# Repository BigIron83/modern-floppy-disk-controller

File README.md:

# Modern Floppy Disk Controller

**Revision B engineering design · 15 November 2026**

Design for a standalone Raspberry Pi OS appliance that captures and replays digital flux-transition timing on conventional 8-inch, 5.25-inch, and 3.5-inch disk drives. The drive supplies the read pulses from its analog read channel. The controller timestamps those pulses and produces timing-accurate write pulses. The Raspberry Pi handles disk formats and stores images locally.

This is an engineering specification. The P1 PCB is routed and documented. Firmware implementation and hardware validation remain pending. Model-specific drive profiles are qualified against the actual drive and manual.

The [Revision P1 hardware package](hardware/p1/README.md) includes the editable KiCad project, Nucleo harness map, and bench validation procedure.

## 1. Architecture

| Layer | Revision B design |
|---|---|
| Appliance | Raspberry Pi 4 Model B or Raspberry Pi 5 running 64-bit Raspberry Pi OS Lite, with local terminal access and optional SSH |
| Pi software | C++17 CLI and shared codec/library code, CMake, Linux spidev |
| Board link | SPI0 over the 40-pin GPIO header, with an active-low reply-ready line and a controller-reset line |
| MCU | STM32H563 with local track memory, hardware timers and DMA. Prototype with NUCLEO-H563ZI plus Pi-header and buffered drive wiring |
| Flux timing | 25 MHz reference timer, 40 ns per tick. Hardware capture of read data and index. Independent hardware compare output and DMA for playback |
| Drive connection | One active drive, keyed 34-pin PC/Shugart connection, and a separate keyed 8-inch 50-pin adapter |
| Power | Independently sized Pi and drive supplies. Pi header supplies controller logic only. Use a common signal ground and protected drive-side buffers |

Select, capture, decode, write, and verify from the Pi. Images are ordinary files on local storage. Linux handles commands and block transfers while the STM32 times read and write edges independently.

## 2. Hardware

### 2.1 Main board

- Pi header prototype map, using BCM GPIO numbering. SPI0 MOSI GPIO10/pin 19, MISO GPIO9/pin 21, SCLK GPIO11/pin 23, CE0 GPIO8/pin 24, REPLY_READY GPIO25/pin 22, CONTROLLER_RESET GPIO24/pin 18, 5 V pin 2 and GND pin 6. Use 3.3 V logic. Verify SPI alternate functions on the selected STM32 package. Hold chip select high and make the controller MISO high impedance while deselected. Drive controller reset with an open-drain stage and default it to released.
- Regulate the Pi header 5 V rail locally to 3.3 V. Budget board current with both Pi models. Keep the drive supply isolated from the Pi supply's positive rails. Include SWD, boot recovery, reset, and test points for SPI, flux timing, index, write data, write gate and hardware permit.
- Use 5 V-tolerant Schmitt receiver inputs with specified partial-power-down behavior, such as SN74LVC14A at 3.3 V. Account for inversion in timer edge selection. Use an optional drive-side pull-up network for open-collector outputs. Size the pull-ups to the drive's sink and cable-edge requirements and power them from the drive-side 5 V domain.
- Use active-low open-drain outputs. Prototype with logic-level NMOS stages qualified for gate drive at 2.5–3.3 V, with gate series resistors and pulldowns. Qualify sink current, low-level voltage, rise time, and released-state leakage on a populated ribbon. A 150 Ω pull-up at 5 V draws about 33 mA per asserted line. Never assume that lightweight CMOS GPIO can sink a vintage termination network. Install the drive terminator per its manual and avoid double termination.
- Give WRITE GATE its own hardware logic AND before the sink driver. Inputs include physical write-enable switch, valid drive-side power, adapter/direct-port permit, a live hardware write-window signal, firmware request, and write-protect clear where the selected drive exposes a valid signal. Pull the output sink off through power-on/reset. Cancel, controller reset, invalid drive state, and watchdog expiry clear the permit. Set the hardware gate deadline before playback starts, independently of DMA or the host.
- A mechanical mode switch or equivalent hardware interlock selects the direct port or the adapter. An adapter ID plus presence and drive-power sensing allows software to reject a profile mismatch. The user connects the drive and sets jumpers with power off. Key connectors, label pin 1, and run signal grounds along the ribbon.
- Externally power the drive from a supply sized for that drive's rails and startup current. Supply drive-side 5 V sensing/reference at a protected dedicated input. Verify drive requirements for 5 V, 12 V, 24 V, and any separate motor supply. Keep cabinet mains and motor wiring within the original or separately engineered drive power assembly.

### 2.2 34-pin connections

All signal names prefixed with / are active low in the standard profiles. Direct-port output mapping is selectable in software with isolated drive outputs for the configurable lines. Use a straight ribbon as the reference setup and qualify a separate PC twisted-cable profile.

| Pin | PC profile | Shugart-style profile |
|---|---|---|
| 2 | Density select, where fitted | Model-specific or unused |
| 8 | /INDEX input | /INDEX input |
| 10, 12, 14, 16 | /MOTOR A, /SELECT B, /SELECT A, /MOTOR B, respectively at controller connector | Commonly /SELECT 0, /SELECT 1, /SELECT 2, /MOTOR, respectively. Confirm drive jumpers |
| 18, 20 | /DIRECTION, /STEP | Same |
| 22, 24 | /WRITE DATA, /WRITE GATE | Same |
| 26, 28, 30 | /TRACK ZERO, /WRITE PROTECT, /READ DATA | Same |
| 32 | /SIDE SELECT | /SIDE SELECT on double-sided drives |
| 34 | Often /DISK CHANGE | Often /READY |
| Odd pins | Signal returns per drive manual and connector key | Same |

Pin 2 drive mode, pin 34 semantics, drive-select jumpers, side select, RPM and step timing belong in each profile. On a typical PC ribbon the twist swaps conductors 10–16. Firmware uses the selected connector/cable position and never asserts both select outputs.

### 2.3 Dedicated 8-inch adapter

Provide a 50-pin keyed connector or keyed IDC-to-edge harness as required. Carry buffered select, direction, step, write data, write gate, and side select, plus separately controllable head load and reduced-write-current/TG43 and profile-specific motor control where supported. Return raw read data, index, track zero, write protect, and ready. Expose additional pins only after checking the specific drive manual.

| SA800-family reference signal | 50-pin assignment to verify against drive |
|---|---|
| Reduced write current | 2, where enabled by the drive's configuration |
| Side select / head load | 14 / 18, where supported |
| Index / ready | 20 / 22 |
| Drive select | 26, 28, 30, or 32, per jumpers |
| Direction / step | 34 / 36 |
| Write data / write gate | 38 / 40 |
| Track zero / write protect / raw read data | 42 / 44 / 46 |

Keep the adapter harness profile-specific. Use the drive's raw read-data path when the manual offers alternate separated outputs or requires a jumper. For an SA800-class drive with a continuously running spindle, apply head load and wait for ready and index under the configured timing. Treat TG43 as a profile rule with a configurable threshold and polarity. Evaluate it from the known physical cylinder after seek, establish it before write gate, and reject writes on drives requiring that signal unless the adapter exposes it. Blank, missing-index, and hard-sectored media require explicit handling.

## 3. Firmware and timing

### 3.1 Capture

1. Select drive, spin up or load head, seek, and confirm the profile's ready criteria. Home by bounded outward stepping against TRACK ZERO. Invalidate the cylinder after reset, failed seek, or unexpected drive change.
2. Capture the active edge of READ DATA and the active edge of INDEX on separate channels of one timer. Use separate DMA rings, record a shared capture epoch and duration, and preserve all index events. Sample independently of buffer boundaries. Reject timer overcapture, DMA overrun, or event-storage exhaustion with a terminal status.
3. Convert consecutive read timestamps into unsigned 16-bit tick deltas. Reserve 0 as an escape followed by a little-endian 32-bit interval. Record first-edge offset and exact capture duration, even for an empty track. Store index offsets separately with 32-bit tick units. At 25 MHz a 32-bit timer wraps in about 172 s. Bound one operation well below that and handle rollover by unsigned subtraction.
4. Support indexed capture, timed capture, and profile-aware hard-sector capture. For hard sectors, retain every physical pulse and identify revolution boundaries from a verified pattern when the drive presents the sector holes. With no compatible index, capture by time and preserve the unaligned origin. Capture one revolution at a time if the requested count exceeds local capacity. Keep continuous and separately reacquired revolutions distinct in the archive.

### 3.2 Playback

1. Upload one complete write plan with intended cylinder/head, start mode, first transition offset, pulse width, intervals, and gate start/stop offsets. Check length, CRC, tick arithmetic, timing limits, and media profile. Apply precompensation at the host before upload when synthesizing a track, with parameters stored in the profile. Preserve source capture and record any changes made for the write.
2. Require physical write enable and explicit host commit, then recheck drive selection, current cylinder/head, power, readiness, index expectations, write protect, and media change. Start from a hardware-synchronized index trigger for indexed writes. Bound the wait for index. Use explicitly defined timed playback only with an appropriate profile and a known write window.
3. Prime the compare timer with the first scheduled edge. A timer compare toggles the write-data output and requests DMA to load the next absolute compare time. Expand compact track intervals into alternating assertion and release times in two small DMA buffers, then refill halves ahead of use. Specify the actual write-data pulse width from the drive manual and program a separately bounded hardware gate window. Use a guard/sentinel and verify service margin with DMA contending for the bus. If the next data block cannot be supplied before its deadline or a timer/DMA fault occurs, force gate inactive and return an incomplete-write status. Playback requires no track data transfers after commit.
4. End at the specified splice within the measured target revolution. Match target RPM where required with explicit host rescaling or regeneration. Abort before writing if the requested window cannot fit. Verify with an independent readback and report sector CRC mismatch or flux-quality differences according to format. A media write can be partial after interruption, so identify the affected track and block automatic retries.

### 3.3 Initial engineering budgets

| Parameter | Design target |
|---|---|
| Timebase | 25 MHz from a crystal-referenced clock tree. Verify actual clock, tick conversion, and temperature behavior |
| Peak event workload | Qualify 1 million flux pulses/s and at least 2 million write compare updates/s for synthetic stress. Pulse width and minimum spacing remain profile-specific |
| DMA load | 4 MB/s for raw read timestamps at the stress rate or 8 MB/s for write compare timestamps. Budget two 1,024-entry 32-bit write DMA halves, each providing approximately 512 µs refill time at 2 million compare events/s |
| Track buffer | 480 KiB design allocation in DMA-eligible SRAM with bank, alignment, and cache/coherency mapping checked before layout signoff. Separate ring buffers, index, SPI, stack and diagnostics allocations |
| Track sizing | At 300 RPM and 1 million pulses/s a revolution is 200 ms and approximately 400 kB at two bytes per pulse. At 360 RPM it is about 333 kB. Sparse long intervals use the escape encoding. Multiple revolutions fit according to actual encoded size |
| Read transfer | Transfer captured blocks after completion. Benchmark sustained SPI throughput on both Pi models. At 4 MHz, the two-transaction framing limits useful throughput to less than 0.25 MB/s. At a measured 0.2 MB/s, a 400 kB revolution takes about 2 s, in addition to seek, acquisition, and rotation wait |

Select TIM2/TIM5 roles, channels, trigger routing and GPDMA requests using the package alternate-function tables, reference manual, and Nucleo board schematic before PCB layout. Prove simultaneous read/index capture and buffered write compare timing on the bench before freezing the design.

## 4. Internal SPI protocol

The Pi is SPI master and the STM32 is slave. Start at 4 MHz, mode 0, MSB first. Qualify higher rates on both Pi models after measuring signal integrity and DMA behavior. Reserve GPIO25 for a reply-ready level asserted only after the MCU has staged a complete response and armed SPI transfer DMA.

**Wire frame.** Little-endian fields in this order. ASCII magic `FDC1` (4 bytes), major and minor version (1 byte each), opcode (uint16), request ID (uint32), payload length (uint32), and payload CRC-32/ISO-HDLC (uint32). Payload follows. A request occupies one 1,024-byte CE0 transaction, padded with zeros. After REPLY_READY asserts, clock a separate 1,024-byte reply transaction with zero-filled MOSI. Limit payloads to 1,004 bytes, including metadata, and validate lengths before use. Replies use opcode bit 15, echo the request ID, and begin with uint16 status and uint16 reserved. Post long operations immediately and poll progress through subsequent commands so cancellation stays available. Keep one command/reply exchange outstanding. After the reply, the MCU deasserts REPLY_READY once the next request receiver is armed. The Pi waits for that level before sending another command. Use offset-addressed data blocks and a CRC over the full staged object.

Unexpected transaction sizes or invalid frames discard the staged command and invalidate write authorization. On timeout, re-establish a known protocol state by controller reset and HELLO. Commit is never automatically retried. Reset drops the gate and invalidates position and write authorization. During an already committed write, the hardware deadline remains effective if the Pi stops communicating.

| Opcode | Operation |
|---|---|
| 0x0001 / 0x0002 | HELLO / GET_STATUS. Return protocol version, board/firmware version, tick rate, limits, adapter identity, drive inputs, and active operation state |
| 0x0010–0x0013 | SET_PROFILE, SELECT_DRIVE, HOME, SEEK. Validate seek bounds, track step multiplier, and profile identity |
| 0x0020–0x0022 | CAPTURE, READ_CAPTURE_BLOCK, RELEASE_CAPTURE. CAPTURE returns an operation handle and completed data stays available until released or session reset |
| 0x0030–0x0033 | BEGIN_WRITE, WRITE_BLOCK, ARM_WRITE, COMMIT_WRITE. Stage by offset, verify full CRC and profile, then issue a short-lived one-use token scoped to the plan and media state |
| 0x0040 | CANCEL. Stop active hardware operation, invalidate write token, and report whether a write window was entered |

Operation errors include invalid profile, no adapter, no index, no ready, write protected, write disabled, invalid timing, geometry limit, overflow, CRC failure, DMA fault, and interrupted write. Poll operation progress with GET_STATUS. Do not automatically replay COMMIT_WRITE after a timeout. A reconnect requires the host to inspect state or read the affected track before a new write attempt. Support recovery firmware update independently of the main protocol, with a physical boot/recovery path.

## 5. Raspberry Pi OS software

- **Operating system.** Qualify a named 64-bit Raspberry Pi OS Lite image on both Pi 4 and Pi 5 and record its release and kernel build. Enable SPI through `raspi-config`. Default to SPI0 CE0 (`/dev/spidev0.0`), with an override for device path and SPI rate. Use libgpiod for reply-ready and controller reset, discovering the header GPIO controller by label or line identifiers. Avoid fixed gpiochip numbers across Pi models.
- **Deployment.** Build a native arm64 package with CMake. Install an unprivileged CLI and grant the operator access to the SPI device and necessary GPIO lines. Serialize hardware access with an exclusive local lock held throughout each operation. Run locally from a terminal or remotely through SSH. Handle terminal hangup by attempting cancellation when the process can still reach the board. Controller-side gate limits apply independently.
- **Commands.** Provide `list`, `drive-test`, `capture`, `decode`, `write`, and `verify`. Add head, cylinder, revolution and profile selection to the media operations. Keep decoding available offline. Require an explicit write command and the physical write-enable switch. Check free space before full-disk capture, retain completed tracks across interruptions, and finalize the archive after validation.
- **Data and profiles.** Save to a user-selected local directory, with support for mounted removable storage. Use versioned drive profiles for geometry, step timing, RPM range, electrical signal roles and write timing. Keep media format definitions separate. Use stable exit codes and machine-readable diagnostics for scripting.

### 5.1 Images and formats

- Archive the raw transition timing and index events first. Keep actual tick rate, cylinder/head, revolution boundaries or capture offsets, profile, RPM estimate, and quality flags with the record. Document the native format and include CRCs. Add SCP import/export with round-trip checks and flag metadata that cannot be preserved in an export.
- Qualify IBM-style FM and MFM sector decode and encode first, then qualify Amiga MFM and Commodore/Apple GCR separately with known-good disks. Preserve sector CRCs and status for reads. Keep standard sector images as derivatives when the format permits them.
- Use a 34-pin drive appropriate to the media when it can physically read and write the format. Original Sony Macintosh mechanisms, Apple Disk II mechanisms and proprietary drives require dedicated electrical adapters where their control interfaces differ. Macintosh 400K/800K variable-speed writes require a qualified mechanism and playback profile. Treat those, 2.88 MB ED, and hard-sector write modes as separately qualified extensions. Preserve multi-revolution variations and report when a drive cannot reproduce observed weak-bit, splice, or protection behavior.
- Match drive head width to the media when writing. In particular, qualify 48-TPI 5.25-inch media in a native 48-TPI mechanism. A 96-TPI drive can double-step for compatible reads but leaves a narrower written track.

## 6. Prototype and acceptance

| Stage | Required evidence |
|---|---|
| Electrical and timing bench | Measure TTL levels, sink current, idle state, rise/fall times, and decode at the drive connector with realistic termination. Inject synthetic read/index patterns through the receiver, sweep minimum pulse width and spacing, and compare timestamps to a calibrated generator. Check repeatable read/write edge error after accounting for fixed propagation delay. Initial acceptance target is ±2 ticks (80 ns) against the fixture, subject to characterization |
| Fail-safe bench | Observe gate at reset, boot, Pi reboot, SPI reset and a stalled Pi process, failed arming, power interruption, write-protect assertion, and forced DMA starvation. Confirm gate never asserts without a valid plan and that active gate clears on detected fault and by the independent deadline. Measure the actual fault-to-gate-off latency |
| 3.5-inch | PC interface HD mechanism. Capture and decode known-good 720 KB and 1.44 MB media, write expendable disks, then verify with an independent controller or legacy system |
| 5.25-inch | Test a native 360 KB drive and a 1.2 MB drive. Verify density, seek and RPM profiles, read at least one original disk per format, and write and independently verify scratch media |
| 8-inch | Qualify an SA800/801-class single-sided FM drive, then a compatible double-sided 8-inch drive for MFM. Verify head load, raw data, ready, index, physical-cylinder tracking, reduced write current behavior across its threshold, and read/write interoperability on scratch disks |
| Pi OS and archival | On both Pi 4 and Pi 5, test startup, SPI detection, transfer under storage and CPU load, cancellation, interrupted SPI, controller reset, and archive round trips. Test missing index, buffer exhaustion, known bad CRC, malformed requests, and Pi reset during a scratch-disk write |

First prototype milestone is a 3.5-inch write/readback on Raspberry Pi OS via SPI to a Nucleo board and 34-pin buffer board, plus timing and gate measurements from a logic analyzer. Bring up 5.25-inch and 8-inch drive profiles on the same firmware before committing to a production PCB. Maintain qualified profile entries by make, model, revision, jumper settings, cable type and supported formats.

## Sources

- [STMicroelectronics STM32H563/573 product line](https://www.st.com/en/microcontrollers-microprocessors/stm32h563-573.html) and [STM32H563 reference documentation](https://www.st.com/en/microcontrollers-microprocessors/stm32h563-573/documentation.html)
- [STMicroelectronics GPDMA application note AN5593](https://www.st.com/resource/en/application_note/an5593-how-to-use-the-gpdma-for-stm32-mcus-stmicroelectronics.pdf)
- [Texas Instruments SN74LVC14A specifications](https://www.ti.com/product/SN74LVC14A)
- [Shugart SA800/801 OEM and service manuals, Bitsavers](https://bitsavers.trailing-edge.com/pdf/shugart/SA8xx/)
- [SA800/801 50-pin interface table](https://allpinouts.org/pinouts/connectors/data_storage/8-floppy-diskdrive/)
- [Greaseweazle raw flux tools](https://github.com/keirf/greaseweazle) and [FluxEngine](https://github.com/davidgiven/fluxengine)
- [Raspberry Pi OS configuration and SPI enablement](https://www.raspberrypi.com/documentation/computers/configuration.html)
- [Raspberry Pi 4 header and GPIO assignments](https://pip-assets.raspberrypi.com/categories/545-raspberry-pi-4-model-b/documents/RP-008341-DS-1-raspberry-pi-4-datasheet.pdf)

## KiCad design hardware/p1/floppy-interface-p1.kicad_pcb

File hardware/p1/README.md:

# Modern Floppy Disk Controller – Routed Interface PCB P1

KiCad 9 routed prototype for the Revision B Raspberry Pi OS appliance. The board is 147 × 138 mm with four M3 mounting holes. It connects by ribbon to the Raspberry Pi 4/5 and by a prototype harness to an STM32H563 Nucleo. The STM32 retains the hardware flux capture, write playback and write deadline. The PCB is a signal interface board with through-hole pads throughout.

## Files

- [Bill of materials](BOM.md) lists quantities and U.S. supplier references for the board and harness.

- `floppy-interface-p1.kicad_pcb` is the editable routed PCB. Open it from `floppy-interface-p1.kicad_pro`.
- `pad-net-map.csv` records footprint pins and intentional no-connect pads.
- `routed-top.png` previews the copper and top silkscreen.
- `floppy-interface-p1.kicad_sch`, `fdc-p1.kicad_sym` and `sym-lib-table` provide the editable schematic and its project-local parts. `schematic.pdf` is the print view.
- `nucleo-j4-harness.csv` specifies the 30 harness positions. `bench-validation.md` covers power selection, bridge settings, timers, DMA and hardware acceptance.
- `erc.txt` and `drc.txt` record ERC, DRC, connectivity and schematic-to-PCB parity.

The board uses two copper layers. Nominal widths are 0.25 mm for signals, 0.60 mm for the +5 V and 3.3 V supplies, and 0.45 mm for ground. Local neck-downs reach 0.15 mm. Nominal routing clearance is 0.22 mm, with 0.60 mm vias and 0.30 mm drills. The bottom layer also has a ground fill.

## Connectors and assembly

| Ref | Connection |
|---|---|
| J1 | Keyed 40-pin cable to the Pi GPIO header. Orient conductor 1 at both ends. |
| J2 | Keyed 34-pin 3.5-inch or 5.25-inch connector. Use a straight ribbon for first bring-up and select the appropriate PC or Shugart profile. |
| J3 | Keyed 50-pin connector for a Shugart-style 8-inch drive. Fit a keyed IDC-to-drive-edge harness when needed. This mapping brings out a single drive-select line on pin 26, head load on pin 18 and TG43/reduced write current on pin 2. Qualify the intended drive's pin functions and jumpers. |
| J4 | Keyed 30-pin STM32 module breakout. This is a custom signal harness. Use the included J4 harness CSV. |
| J5 | Drive-side regulated +5 V sense/pull-up input, pin 1 positive, pin 2 ground. Drive power is supplied separately. |
| JP1 | Physical write-enable shunt. Default assembly is shunt removed. |
| TP1–TP6 | Index, read data, write data, write gate, write window, and ground. |

J1–J4 use square pin-1 pads, silkscreen numerals and connector orientation marks. J5 and JP1 have a pin-1 numeral. U1–U5 show pin 1 and the package notch. Verify the shroud key and red stripe on each actual cable.

Connect **one drive at a time**, with both systems powered off while changing cables. The two drive headers share drive signals. The 8-inch spindle/head-load arrangement is intended for the SA800-style baseline and must be checked for the actual mechanism. The 8-inch interface does not provide general-purpose motor-on or special control signals on optional pins. J5 takes the drive's regulated logic rail. It does not feed drive motor or logic power. Keep Pi and drive positive rails separate, with a common signal ground.

## Parts and circuit

| References | Preliminary parts |
|---|---|
| U1–U2 | Socketed SN74LS06N PDIP open-collector drivers. Check sink current and VOL against the selected drive termination. |
| U3–U4 | SN74LVC14A on pin-for-pin SOIC-14 to DIP-14 carriers. The carrier leads are through-hole at the baseboard. Verify carrier envelope and orientation. These two modules and the STM32 development board contain the surface-mount devices in the design. |
| U5 | Socketed CD74HCT21E PDIP gate for firmware request, timer window, physical arm and write-protect clear. Verify thresholds, propagation and power-up behavior. |
| RN1–RN2 | Bussed 1 kΩ ×6 SIP pulldowns, common at pin 1. Check the selected MCU GPIO drive budget against simultaneous assertions. |
| RN3 | Bussed 2.2 kΩ ×6 SIP drive-input pull-ups, common to DRIVE_5V at pin 1. Check original drive output type and termination. Recalculate if the actual pull-up configuration differs. |
| R1–R8, Q1, C1–C5 | Axial resistors, pinout-qualified TO-92 reset MOSFET and radial 100 nF ceramic bypass capacitors. The TO-92 footprint expects source, gate, drain on pads 1, 2, 3. |
| J1–J5, JP1, TP1–TP6 | Through-hole keyed headers, shunt and test pads. |

Receiver outputs are inverted relative to the active-low drive lines. The drive +5 V sense path produces the source for the write-enable jumper through two receive gates. The write gate is active low at the connector. Drive-side write protect is interpreted as asserted low. With no drive connected, the pull-up can indicate a clear write-protect state, so firmware must also validate drive selection and media state before arming.

## Verification and prototype status

KiCad ERC and DRC completed with zero reported violations, zero unresolved connections, and zero schematic-parity differences. All 284 numbered pads were compared with the schematic and original pin map, including intentional no-connects. PCB copper routes and connector placement were preserved.

The Nucleo harness assignments and peripheral functions were checked against ST's documentation. The board and harness still require assembly and physical validation. Follow the bench validation procedure before attaching archival media.

## References

- [Shugart SA800/801 OEM and service manuals](https://bitsavers.trailing-edge.com/pdf/shugart/SA8xx/)
- [SA800-family interface reference](https://allpinouts.org/pinouts/connectors/data_storage/8-floppy-diskdrive/)
- [STM32H563 Nucleo board](https://www.st.com/en/evaluation-tools/nucleo-h563zi.html)
- [Raspberry Pi GPIO header documentation](https://www.raspberrypi.com/documentation/computers/raspberry-pi.html)
- [TI SN74LS06](https://www.ti.com/product/SN74LS06), [TI SN74LVC14A](https://www.ti.com/product/SN74LVC14A), [TI CD74HCT21](https://www.ti.com/lit/ds/symlink/cd74hct21.pdf)

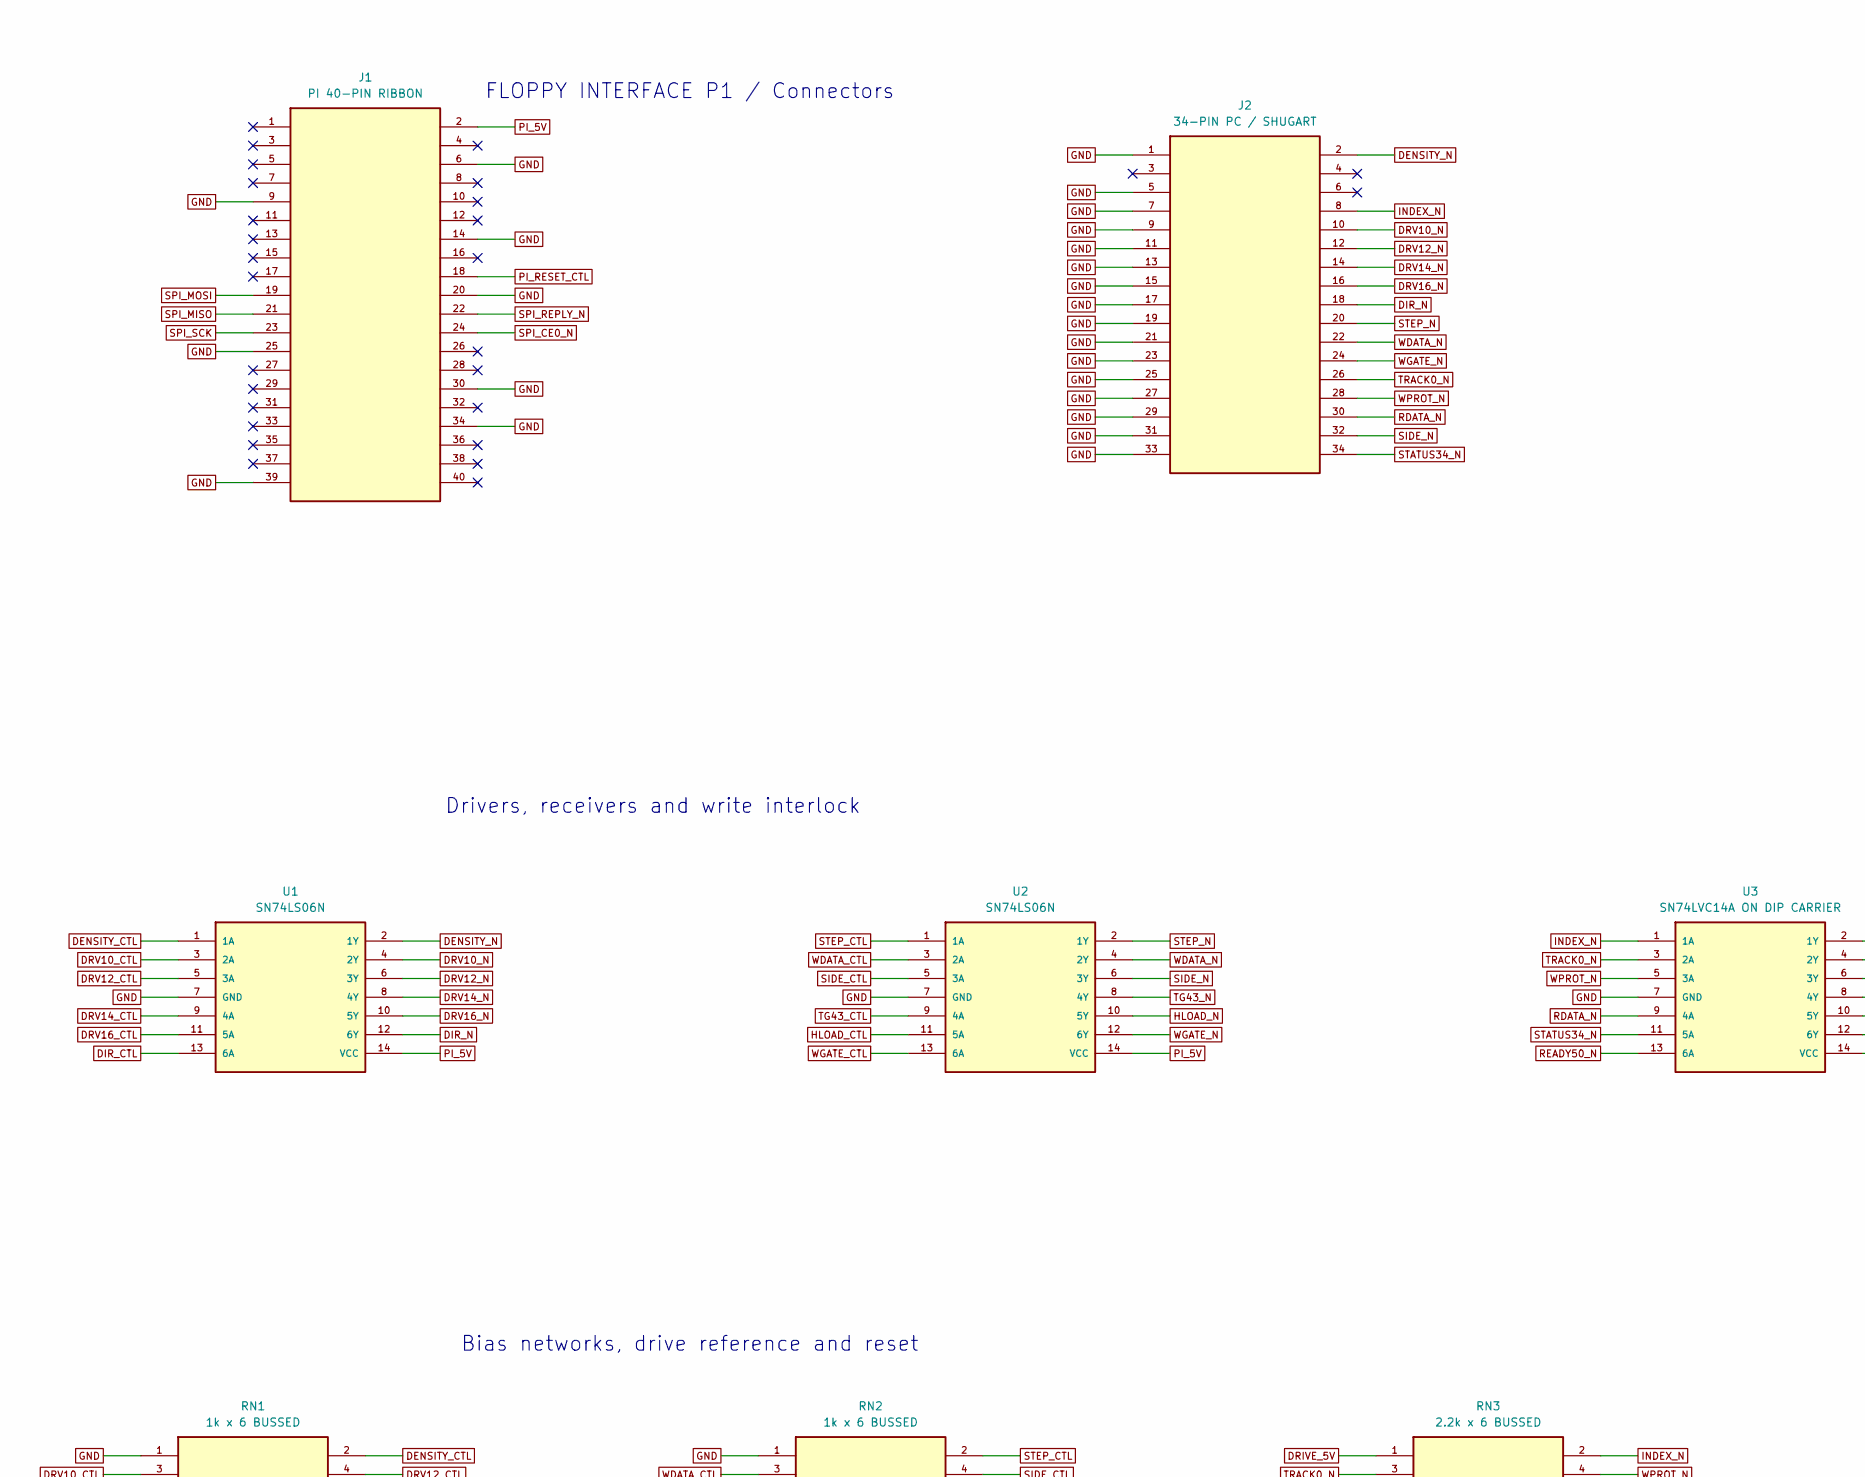
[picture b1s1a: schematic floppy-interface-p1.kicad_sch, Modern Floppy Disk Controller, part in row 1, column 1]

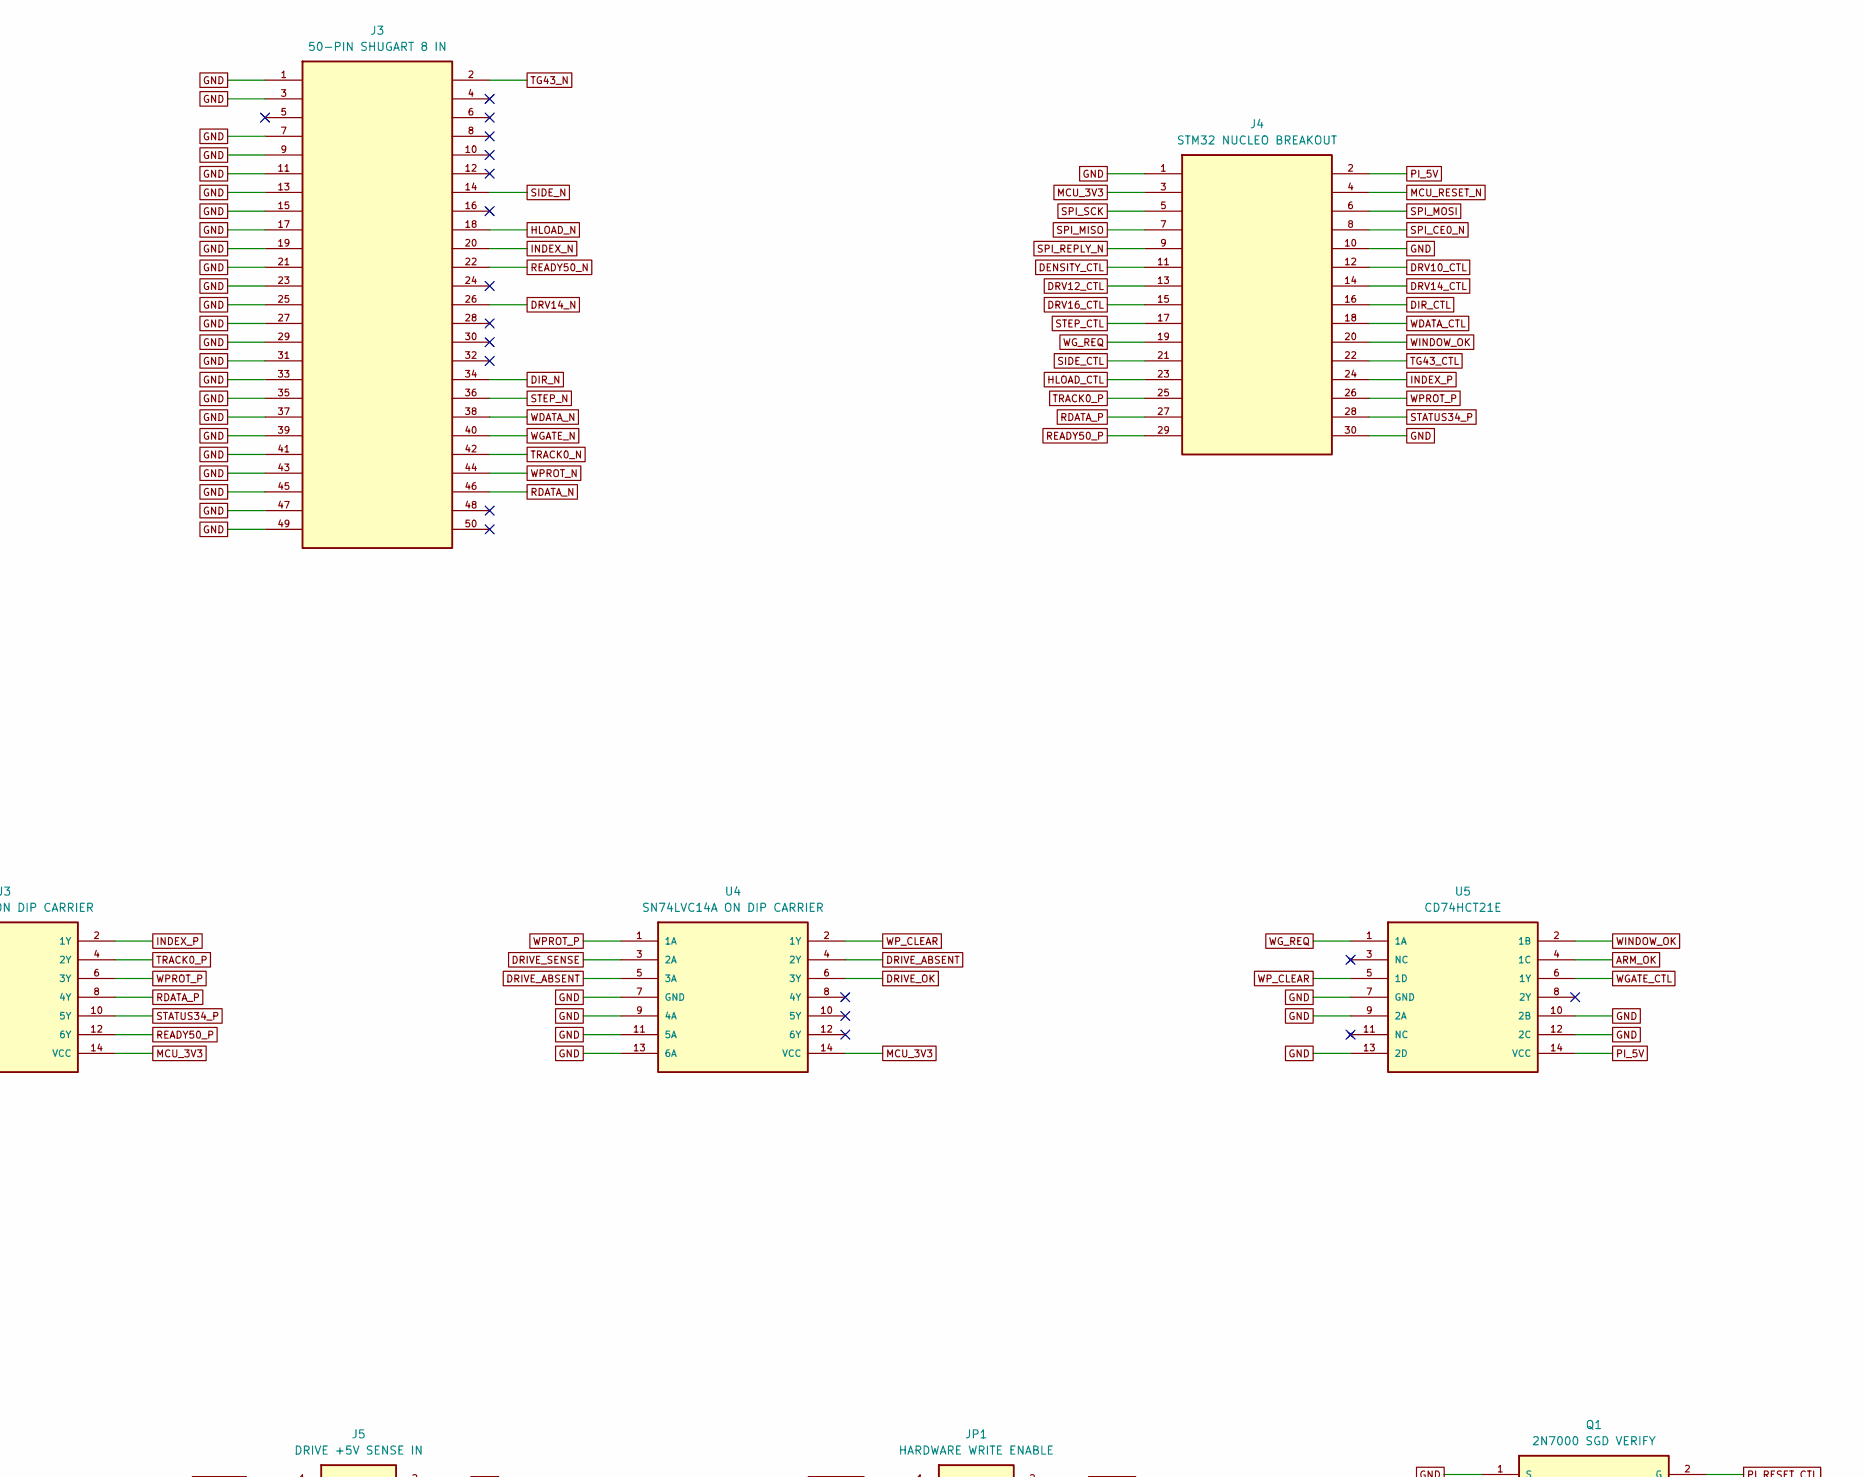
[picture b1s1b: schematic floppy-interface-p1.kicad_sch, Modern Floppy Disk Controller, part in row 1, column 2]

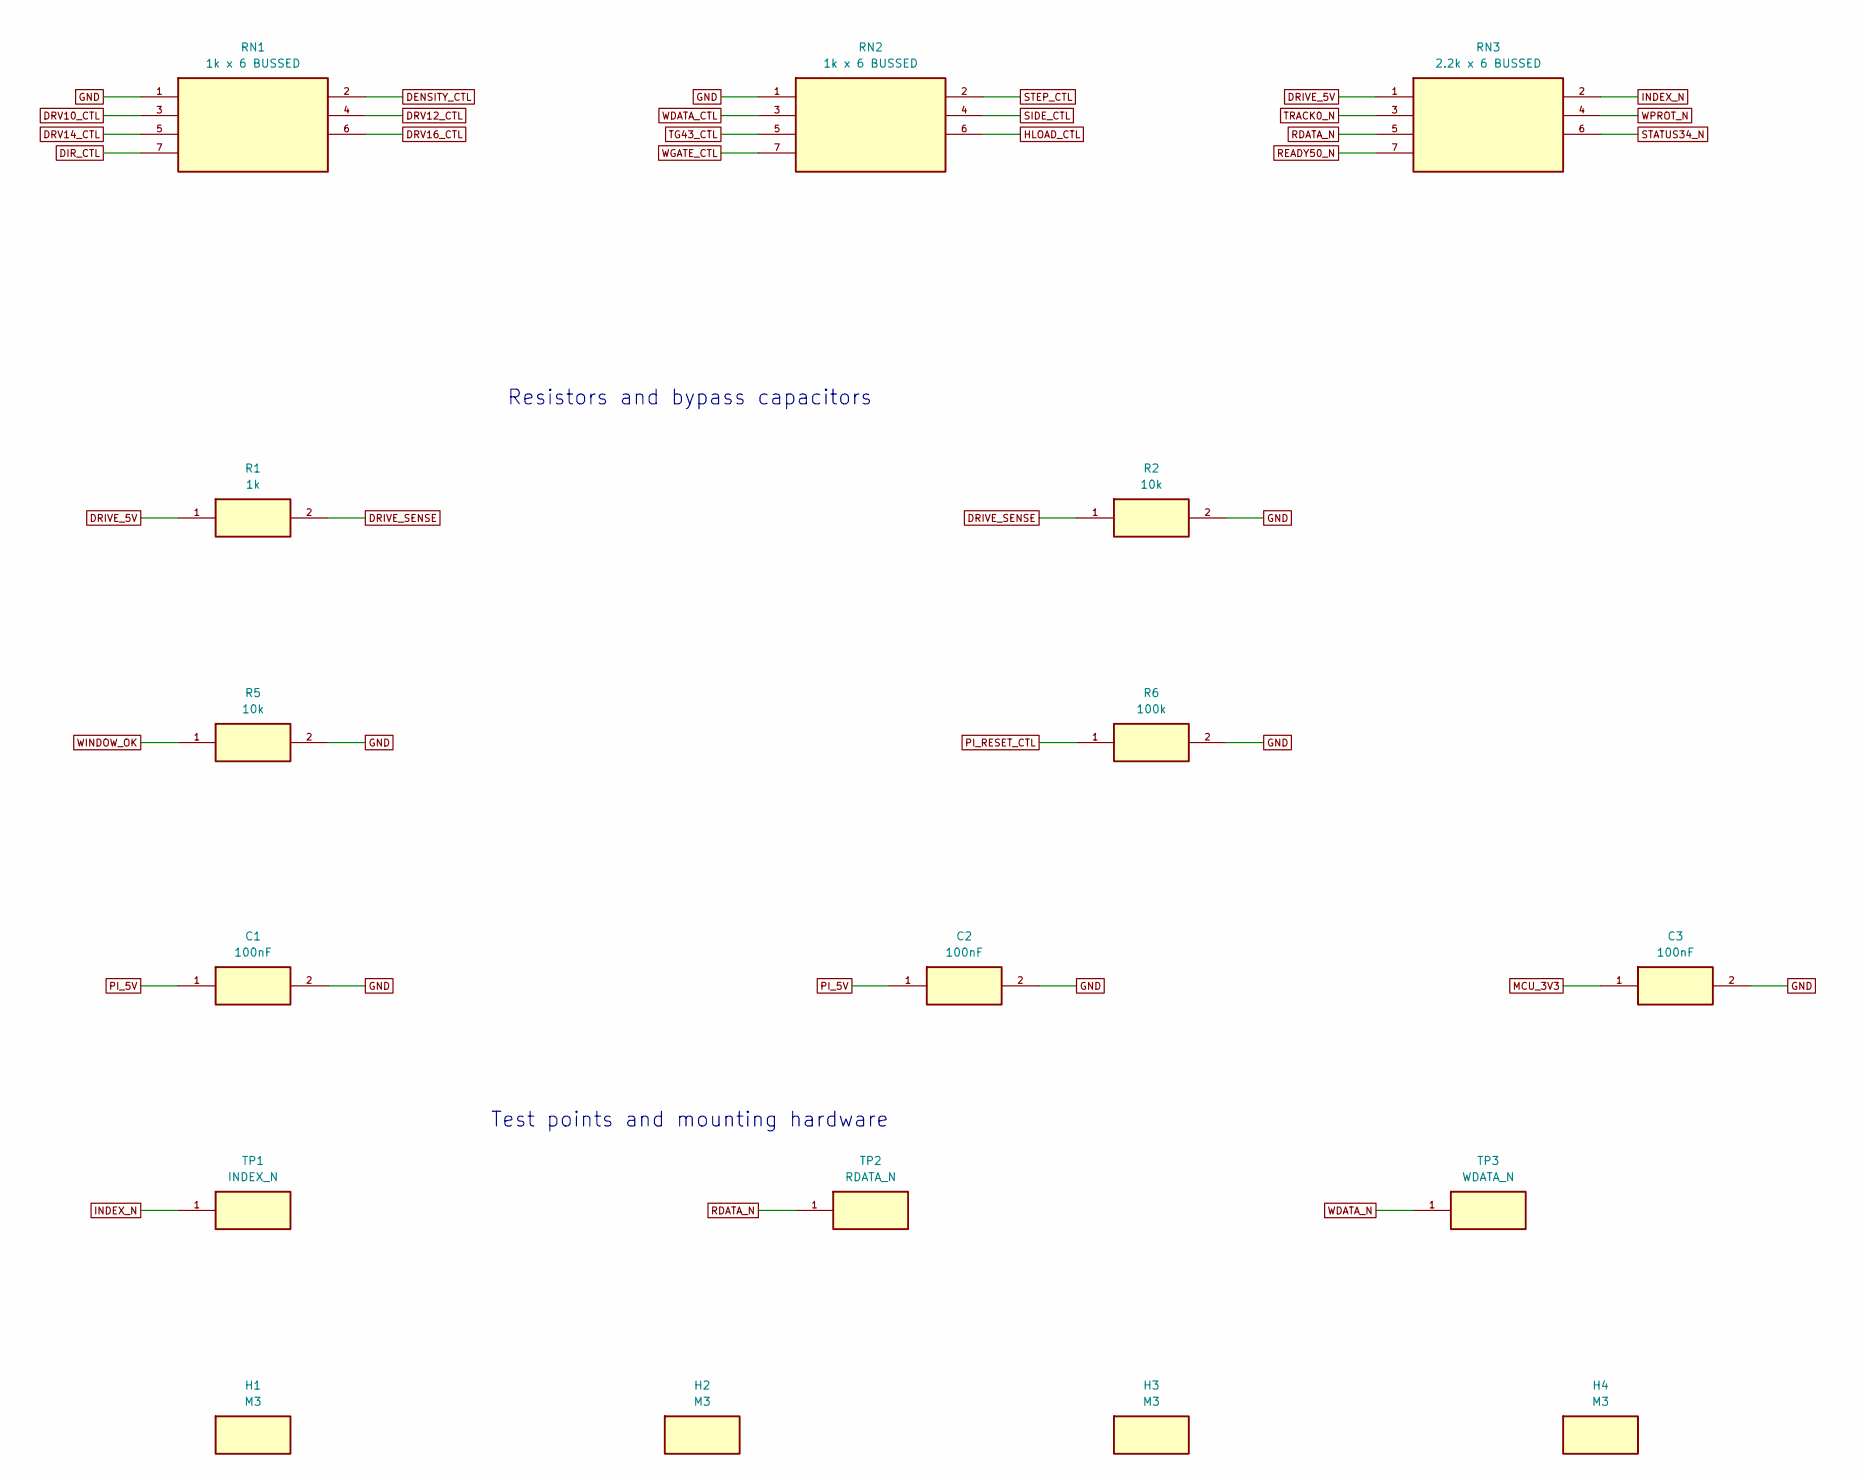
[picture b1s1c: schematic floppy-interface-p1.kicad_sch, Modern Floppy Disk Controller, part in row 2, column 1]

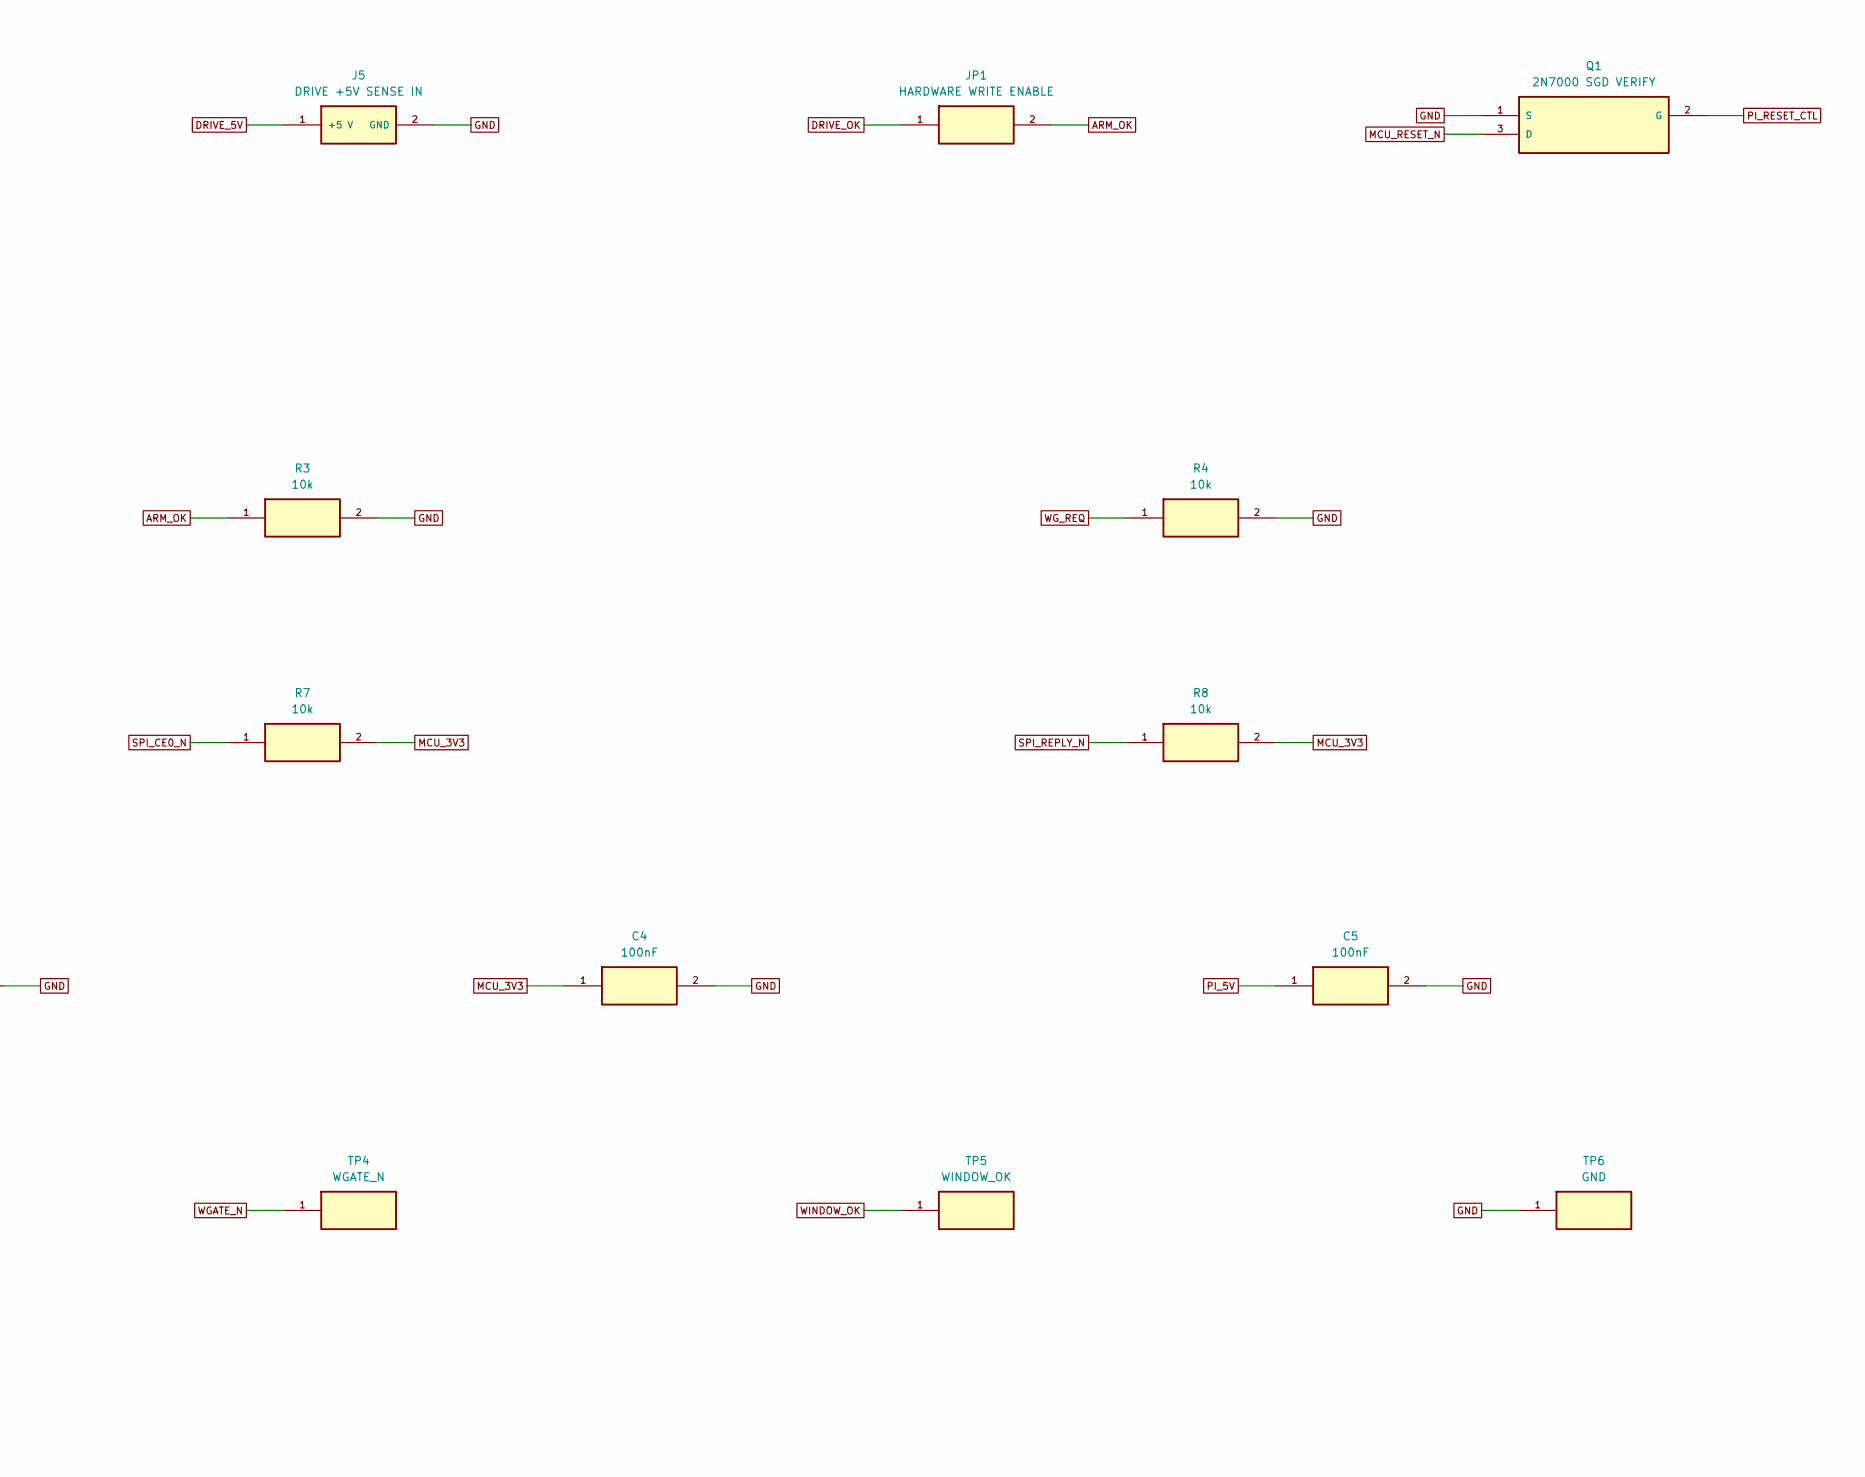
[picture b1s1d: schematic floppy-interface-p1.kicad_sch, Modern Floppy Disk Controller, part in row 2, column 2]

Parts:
C1, C2, C3, C4, C5: 100nF; C_Disc_D5.0mm_W2.5mm_P2.50mm
H1, H2, H3, H4: M3; MountingHole_3.2mm_M3
J1: PI 40-PIN RIBBON; IDC-Header_2x20_P2.54mm_Vertical
J2: 34-PIN PC / SHUGART; IDC-Header_2x17_P2.54mm_Vertical
J3: 50-PIN SHUGART 8 IN; IDC-Header_2x25_P2.54mm_Vertical
J4: STM32 NUCLEO BREAKOUT; IDC-Header_2x15_P2.54mm_Vertical
J5: DRIVE +5V SENSE IN; JST_XH_B2B-XH-A_1x02_P2.50mm_Vertical
JP1: HARDWARE WRITE ENABLE; PinHeader_1x02_P2.54mm_Vertical
Q1: 2N7000 SGD VERIFY; TO-92_Inline_Wide
R1: 1k; R_Axial_DIN0207_L6.3mm_D2.5mm_P7.62mm_Horizontal
R2, R3, R4, R5, R7, R8: 10k; R_Axial_DIN0207_L6.3mm_D2.5mm_P7.62mm_Horizontal
R6: 100k; R_Axial_DIN0207_L6.3mm_D2.5mm_P7.62mm_Horizontal
RN1, RN2: 1k x 6 BUSSED; R_Array_SIP7
RN3: 2.2k x 6 BUSSED; R_Array_SIP7
TP1: INDEX_N; TestPoint_THTPad_D2.0mm_Drill1.0mm
TP2: RDATA_N; TestPoint_THTPad_D2.0mm_Drill1.0mm
TP3: WDATA_N; TestPoint_THTPad_D2.0mm_Drill1.0mm
TP4: WGATE_N; TestPoint_THTPad_D2.0mm_Drill1.0mm
TP5: WINDOW_OK; TestPoint_THTPad_D2.0mm_Drill1.0mm
TP6: GND; TestPoint_THTPad_D2.0mm_Drill1.0mm
U1, U2: SN74LS06N; DIP-14_W7.62mm
U3, U4: SN74LVC14A ON DIP CARRIER; DIP-14_W7.62mm
U5: CD74HCT21E; DIP-14_W7.62mm

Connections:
ARM_OK: JP1.2, R3.1, U5.4 (1C)
DENSITY_CTL: J4.11, RN1.2, U1.1 (1A)
DENSITY_N: J2.2, U1.2 (1Y)
DIR_CTL: J4.16, RN1.7, U1.13 (6A)
DIR_N: J2.18, J3.34, U1.12 (6Y)
DRIVE_5V: J5.1 (+5 V), R1.1, RN3.1
DRIVE_ABSENT: U4.4 (2Y), U4.5 (3A)
DRIVE_OK: JP1.1, U4.6 (3Y)
DRIVE_SENSE: R1.2, R2.1, U4.3 (2A)
DRV10_CTL: J4.12, RN1.3, U1.3 (2A)
DRV10_N: J2.10, U1.4 (2Y)
DRV12_CTL: J4.13, RN1.4, U1.5 (3A)
DRV12_N: J2.12, U1.6 (3Y)
DRV14_CTL: J4.14, RN1.5, U1.9 (4A)
DRV14_N: J2.14, J3.26, U1.8 (4Y)
DRV16_CTL: J4.15, RN1.6, U1.11 (5A)
DRV16_N: J2.16, U1.10 (5Y)
GND: C1.2, C2.2, C3.2, C4.2, C5.2, J1.6, J1.9, J1.14, J1.20, J1.25, J1.30, J1.34, J1.39, J2.1, J2.5, J2.7, J2.9, J2.11, J2.13, J2.15, J2.17, J2.19, J2.21, J2.23, J2.25, J2.27, J2.29, J2.31, J2.33, J3.1, J3.3, J3.7, J3.9, J3.11, J3.13, J3.15, J3.17, J3.19, J3.21, J3.23, J3.25, J3.27, J3.29, J3.31, J3.33, J3.35, J3.37, J3.39, J3.41, J3.43, J3.45, J3.47, J3.49, J4.1, J4.10, J4.30, J5.2 (GND), Q1.1 (S), R2.2, R3.2, R4.2, R5.2, R6.2, RN1.1, RN2.1, TP6.1, U1.7 (GND), U2.7 (GND), U3.7 (GND), U4.7 (GND), U4.9 (4A), U4.11 (5A), U4.13 (6A), U5.7 (GND), U5.9 (2A), U5.10 (2B), U5.12 (2C), U5.13 (2D)
HLOAD_CTL: J4.23, RN2.6, U2.11 (5A)
HLOAD_N: J3.18, U2.10 (5Y)
INDEX_N: J2.8, J3.20, RN3.2, TP1.1, U3.1 (1A)
INDEX_P: J4.24, U3.2 (1Y)
MCU_3V3: C3.1, C4.1, J4.3, R7.2, R8.2, U3.14 (VCC), U4.14 (VCC)
MCU_RESET_N: J4.4, Q1.3 (D)
PI_5V: C1.1, C2.1, C5.1, J1.2, J4.2, U1.14 (VCC), U2.14 (VCC), U5.14 (VCC)
PI_RESET_CTL: J1.18, Q1.2 (G), R6.1
RDATA_N: J2.30, J3.46, RN3.5, TP2.1, U3.9 (4A)
RDATA_P: J4.27, U3.8 (4Y)
READY50_N: J3.22, RN3.7, U3.13 (6A)
READY50_P: J4.29, U3.12 (6Y)
SIDE_CTL: J4.21, RN2.4, U2.5 (3A)
SIDE_N: J2.32, J3.14, U2.6 (3Y)
SPI_CE0_N: J1.24, J4.8, R7.1
SPI_MISO: J1.21, J4.7
SPI_MOSI: J1.19, J4.6
SPI_REPLY_N: J1.22, J4.9, R8.1
SPI_SCK: J1.23, J4.5
STATUS34_N: J2.34, RN3.6, U3.11 (5A)
STATUS34_P: J4.28, U3.10 (5Y)
STEP_CTL: J4.17, RN2.2, U2.1 (1A)
STEP_N: J2.20, J3.36, U2.2 (1Y)
TG43_CTL: J4.22, RN2.5, U2.9 (4A)
TG43_N: J3.2, U2.8 (4Y)
TRACK0_N: J2.26, J3.42, RN3.3, U3.3 (2A)
TRACK0_P: J4.25, U3.4 (2Y)
WDATA_CTL: J4.18, RN2.3, U2.3 (2A)
WDATA_N: J2.22, J3.38, TP3.1, U2.4 (2Y)
WGATE_CTL: RN2.7, U2.13 (6A), U5.6 (1Y)
WGATE_N: J2.24, J3.40, TP4.1, U2.12 (6Y)
WG_REQ: J4.19, R4.1, U5.1 (1A)
WINDOW_OK: J4.20, R5.1, TP5.1, U5.2 (1B)
WPROT_N: J2.28, J3.44, RN3.4, U3.5 (3A)
WPROT_P: J4.26, U3.6 (3Y), U4.1 (1A)
WP_CLEAR: U4.2 (1Y), U5.5 (1D)

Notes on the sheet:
FLOPPY INTERFACE P1 / Connectors
Drivers, receivers and write interlock
Bias networks, drive reference and reset
Resistors and bypass capacitors
Test points and mounting hardware

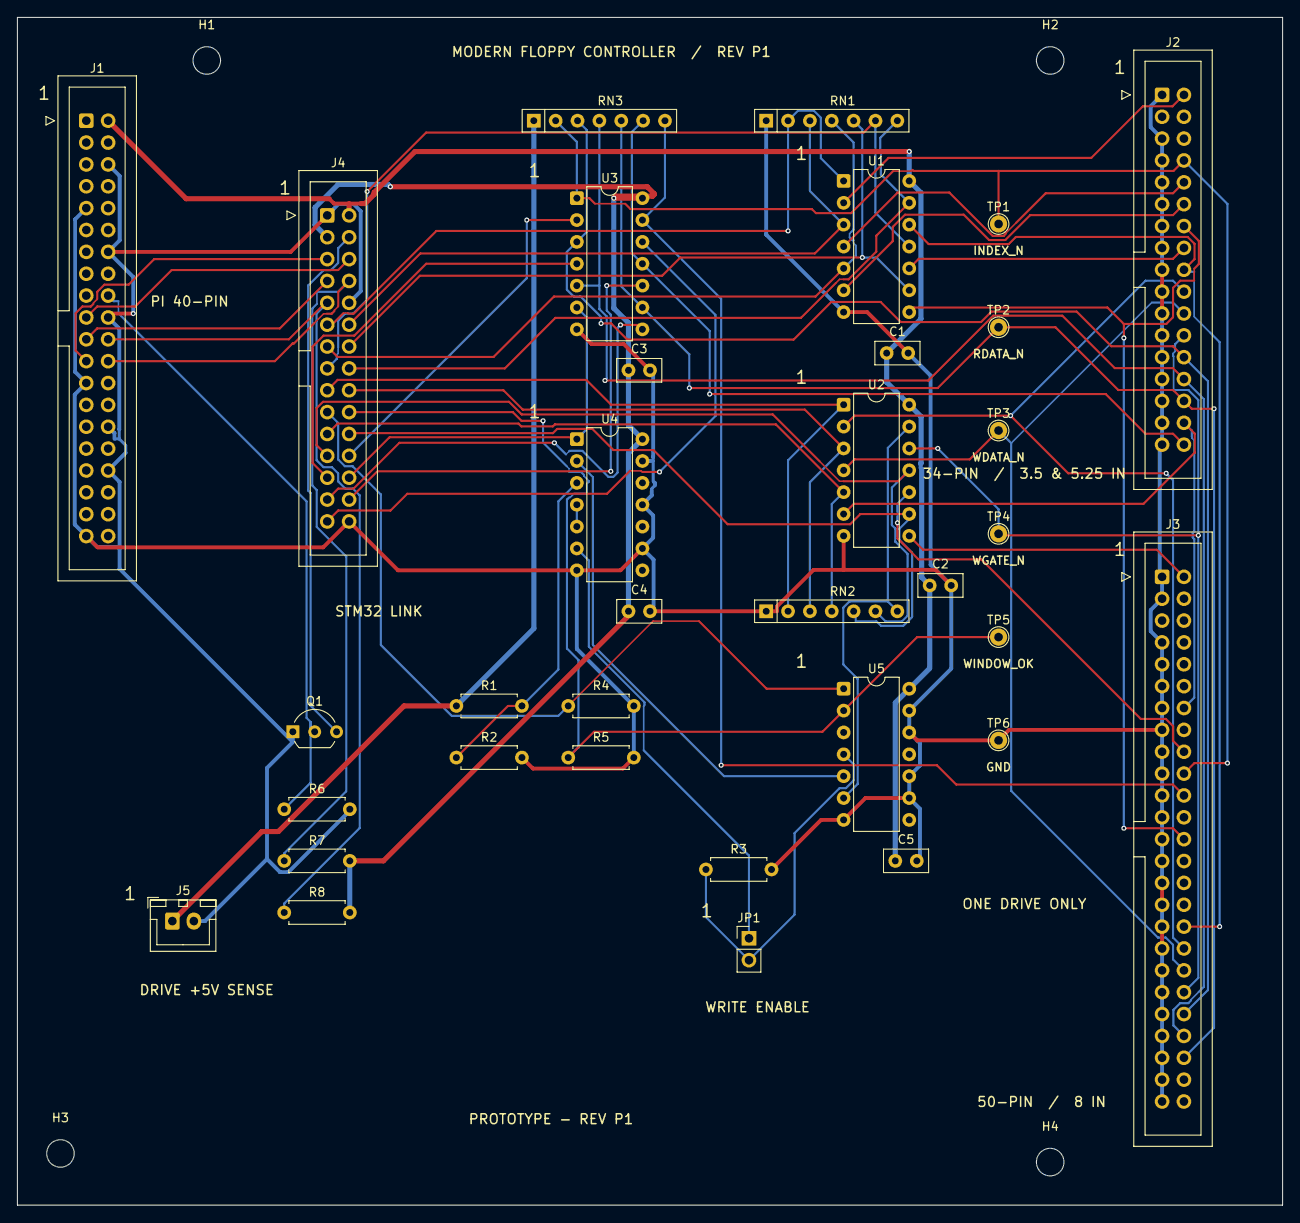
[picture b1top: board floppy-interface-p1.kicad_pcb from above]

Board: 2 copper layers, 147.0 x 138.0 mm, 38 parts (0 on the bottom side), 54 nets.
